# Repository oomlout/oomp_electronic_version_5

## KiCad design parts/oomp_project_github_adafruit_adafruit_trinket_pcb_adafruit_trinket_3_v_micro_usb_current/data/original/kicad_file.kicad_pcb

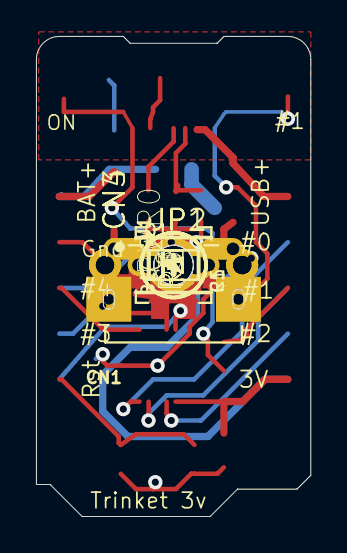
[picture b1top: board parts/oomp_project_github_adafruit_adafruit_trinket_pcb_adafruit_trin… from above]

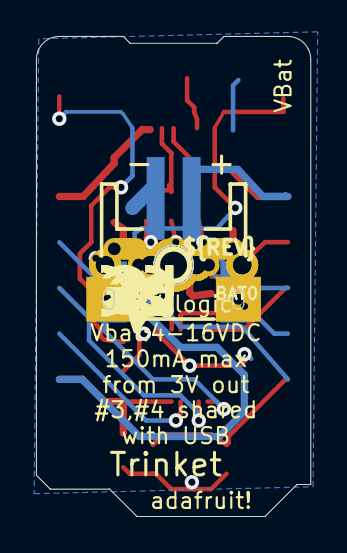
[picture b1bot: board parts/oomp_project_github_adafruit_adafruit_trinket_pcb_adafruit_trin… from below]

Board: 16 copper layers, 15.2 x 26.7 mm, 30 parts (5 on the bottom side), 15 nets.

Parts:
B1: red; CHIPLED_0805_NOOUTLINE
BAT0: JSTPH2
C1, C8: 10uF; 0805-NO
CN1: 4UCONN_20329
CN3, CN4: 1X4-CLEANBIG; 1X04-CLEANBIG
D2, D3: SCHOTTKY; SOD-123FL
IC2: MIC5225-3.3v; SOT23-5L
JP1, JP2: 1X01-CLEANBIG
PWR0: green; CHIPLED_0805_NOOUTLINE
Q1: reset; BTN_KMR2_4.6X2.8
R1, R2: 68 (0603); 0603-NO
R3: 1.5K (0603); 0603-NO
R4, R5: 470 (0603); 0603-NO
U1: MLF20_4X4MM_0.5MM_ATMEL
U$1, U$6: FIDUCIAL""; FIDUCIAL_1MM
U$5: ADAFRUIT_3.5MM
U$8, U$9: MOUNTINGHOLE2.0; MOUNTINGHOLE_2.0_PLATED
U$12: PCBFEAT-REV-040
U$13: SYMBOL_FCC_TINY
U$14: SYMBOL_CE_TINY
UNK_HOLE_0: dummyfp0
UNK_HOLE_1: dummyfp1

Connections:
+3V3: C8.1, CN4.1, IC2.5, R3.2, R4.2, U1.15
B0: CN4.4, U1.11
B1: CN4.3, R5.2, U1.12
B2: CN4.2, U1.14
B3: CN3.2, R1.2, U1.2
B4: CN3.3, R2.2, U1.5
D+: CN1.D+, R2.1
D-: CN1.D-, R1.1, R3.1
GND: B1.C, BAT0.1, C1.2, C8.2, CN1.BASE@1, CN1.BASE@2, CN1.GND, CN1.SPRT@1, CN1.SPRT@2, CN1.SPRT@3, CN1.SPRT@4, CN3.4, IC2.2, PWR0.C, Q1.B, Q1.B', U1.8, U1.THERMAL
unnamed: B1.A, R5.1
unnamed: PWR0.A, R4.1
unnamed: C1.1, D2.C, D3.C, IC2.1, IC2.3
RESET: CN3.1, Q1.A, Q1.A', U1.1
VBAT: BAT0.2, D3.A, JP2.1
VBUS: CN1.VBUS, D2.A, JP1.1

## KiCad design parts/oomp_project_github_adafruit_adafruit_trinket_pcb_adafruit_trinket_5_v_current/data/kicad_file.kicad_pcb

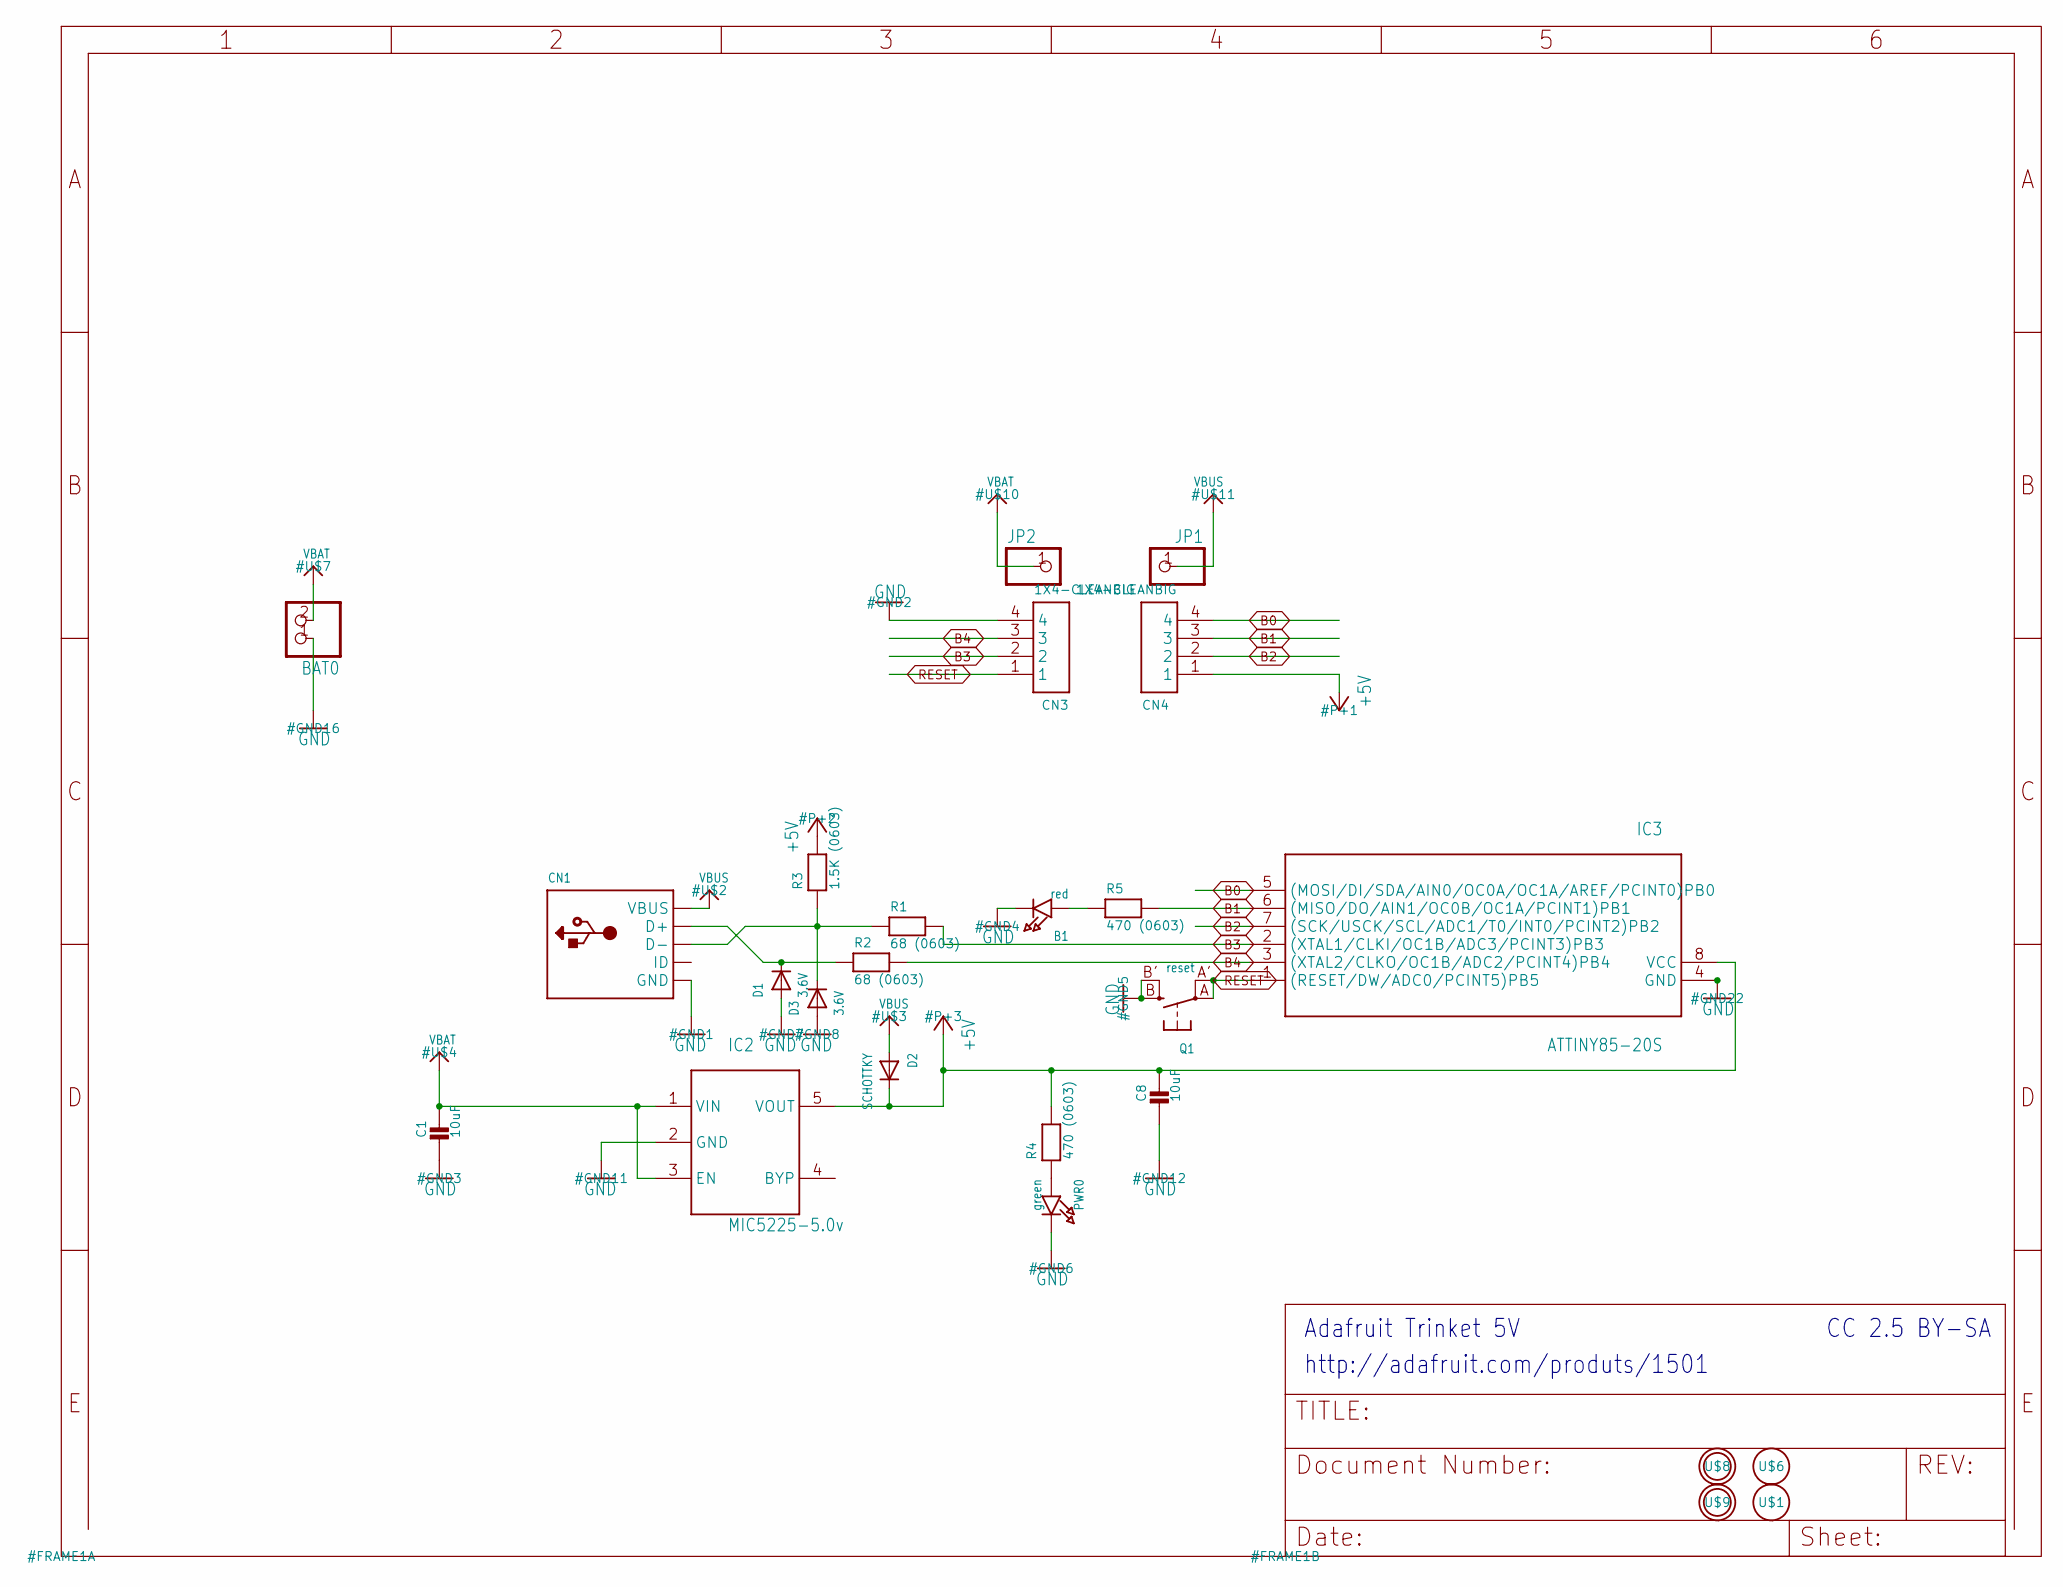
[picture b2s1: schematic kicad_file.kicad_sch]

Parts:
B1: red; CHIPLED_0805_NOOUTLINE
BAT0: CON_JST_PH_2PIN; JSTPH2
C1, C8: 10uF; 0805-NO
CN1: USBMINIB; USB-MINIB
CN3, CN4: 1X4-CLEANBIG; 1X04-CLEANBIG
D1, D3: 3.6V; SOD-323
D2: SCHOTTKY; SOD-123FL
IC2: MIC5225-5.0v; SOT23-5L
IC3: ATTINY85-20S; SOIC8
JP1, JP2: PINHD-1X1CB; 1X01-CLEANBIG
PWR0: green; CHIPLED_0805_NOOUTLINE
Q1: reset; BTN_KMR2_4.6X2.8
R1, R2: 68 (0603); 0603-NO
R3: 1.5K (0603); 0603-NO
R4, R5: 470 (0603); 0603-NO
U$1, U$6: FIDUCIAL; FIDUCIAL_1MM
U$8, U$9: MOUNTINGHOLE2.0; MOUNTINGHOLE_2.0_PLATED

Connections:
+5V: C8.1, CN4.1, D2.C, IC2.5 (VOUT), IC3.8 (VCC), R3.2, R4.2
B0: CN4.4, IC3.5 ((MOSI/DI/SDA/AIN0/OC0A/OC1A/AREF/PCINT0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)
B1: CN4.3, IC3.6 ((MISO/DO/AIN1/OC0B/OC1A/PCINT1)PB1), R5.2
B2: CN4.2, IC3.7 ((SCK/USCK/SCL/ADC1/T0/INT0/PCINT2)PB2)
B3: CN3.2, IC3.2 ((XTAL1/CLKI/OC1B/ADC3/PCINT3)PB3), R1.2
B4: CN3.3, IC3.3 ((XTAL2/CLKO/OC1B/ADC2/PCINT4)PB4), R2.2
GND: B1.C, BAT0.1, C1.2, C8.2, CN1.GND, CN1.GND1 (GND), CN1.GND2 (GND), CN1.GND3 (GND), CN1.GND4 (GND), CN3.4, D1.A, D3.A, IC2.2 (GND), IC3.4 (GND), PWR0.C, Q1.B (S), Q1.B' (S1)
unnamed: B1.A, R5.1
unnamed: CN1.D+, D1.C, R2.1
unnamed: CN1.D-, D3.C, R1.1, R3.1
unnamed: PWR0.A, R4.1
RESET: CN3.1, IC3.1 ((RESET/DW/ADC0/PCINT5)PB5), Q1.A, Q1.A' (P1)
VBAT: BAT0.2, C1.1, IC2.1 (VIN), IC2.3 (EN), JP2.1
VBUS: CN1.VBUS, D2.A, JP1.1

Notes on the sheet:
CC 2.5 BY-SA
Adafruit Trinket 5V
http://adafruit.com/produts/1501

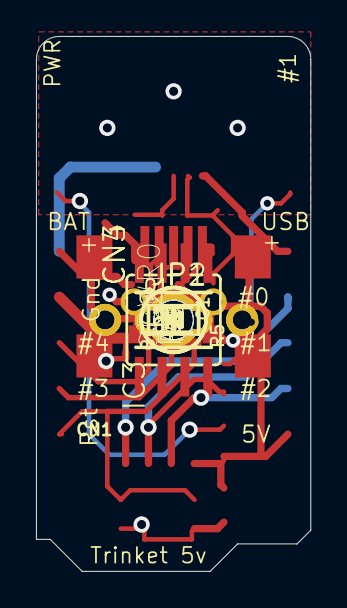
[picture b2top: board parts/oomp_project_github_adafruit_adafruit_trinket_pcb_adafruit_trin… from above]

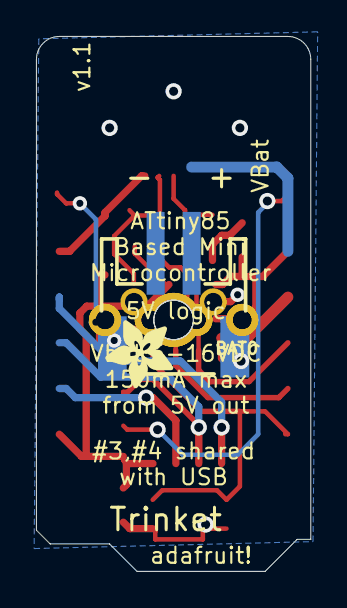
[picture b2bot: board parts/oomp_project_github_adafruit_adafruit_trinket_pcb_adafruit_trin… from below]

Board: 16 copper layers, 15.2 x 29.7 mm, 28 parts (2 on the bottom side), 14 nets.

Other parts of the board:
U$5: ADAFRUIT_3.5MM
UNK_HOLE_0: dummyfp0
UNK_HOLE_1: dummyfp1

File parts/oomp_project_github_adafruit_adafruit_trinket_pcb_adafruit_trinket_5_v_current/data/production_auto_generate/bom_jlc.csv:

Comment,Designator,Footprint,LCSC Part #
,"JP1,JP2",Adafruit Trinket 5V-import-fps:1X01-CLEANBIG,C7501259
,U$5,Adafruit Trinket 5V-import-fps:ADAFRUIT_3.5MM,
,BAT0,Adafruit Trinket 5V-import-fps:JSTPH2,
,CN1,Adafruit Trinket 5V-import-fps:USB-MINIB,
1.5K (0603),R3,Adafruit Trinket 5V-import-fps:0603-NO,C2930050
10uF,"C1,C8",Adafruit Trinket 5V-import-fps:0805-NO,
1X4-CLEANBIG,"CN3,CN4",Adafruit Trinket 5V-import-fps:1X04-CLEANBIG,
3.6V,"D1,D3",Adafruit Trinket 5V-import-fps:SOD-323,
470 (0603),"R4,R5",Adafruit Trinket 5V-import-fps:0603-NO,C23179
68 (0603),"R1,R2",Adafruit Trinket 5V-import-fps:0603-NO,C27592
ATTINY85-20S,IC3,Adafruit Trinket 5V-import-fps:SOIC8,
FIDUCIAL,"U$1,U$6",Adafruit Trinket 5V-import-fps:FIDUCIAL_1MM,
green,PWR0,Adafruit Trinket 5V-import-fps:CHIPLED_0805_NOOUTLINE,
MIC5225-5.0v,IC2,Adafruit Trinket 5V-import-fps:SOT23-5L,
red,B1,Adafruit Trinket 5V-import-fps:CHIPLED_0805_NOOUTLINE,
reset,Q1,Adafruit Trinket 5V-import-fps:BTN_KMR2_4.6X2.8,
SCHOTTKY,D2,Adafruit Trinket 5V-import-fps:SOD-123FL,

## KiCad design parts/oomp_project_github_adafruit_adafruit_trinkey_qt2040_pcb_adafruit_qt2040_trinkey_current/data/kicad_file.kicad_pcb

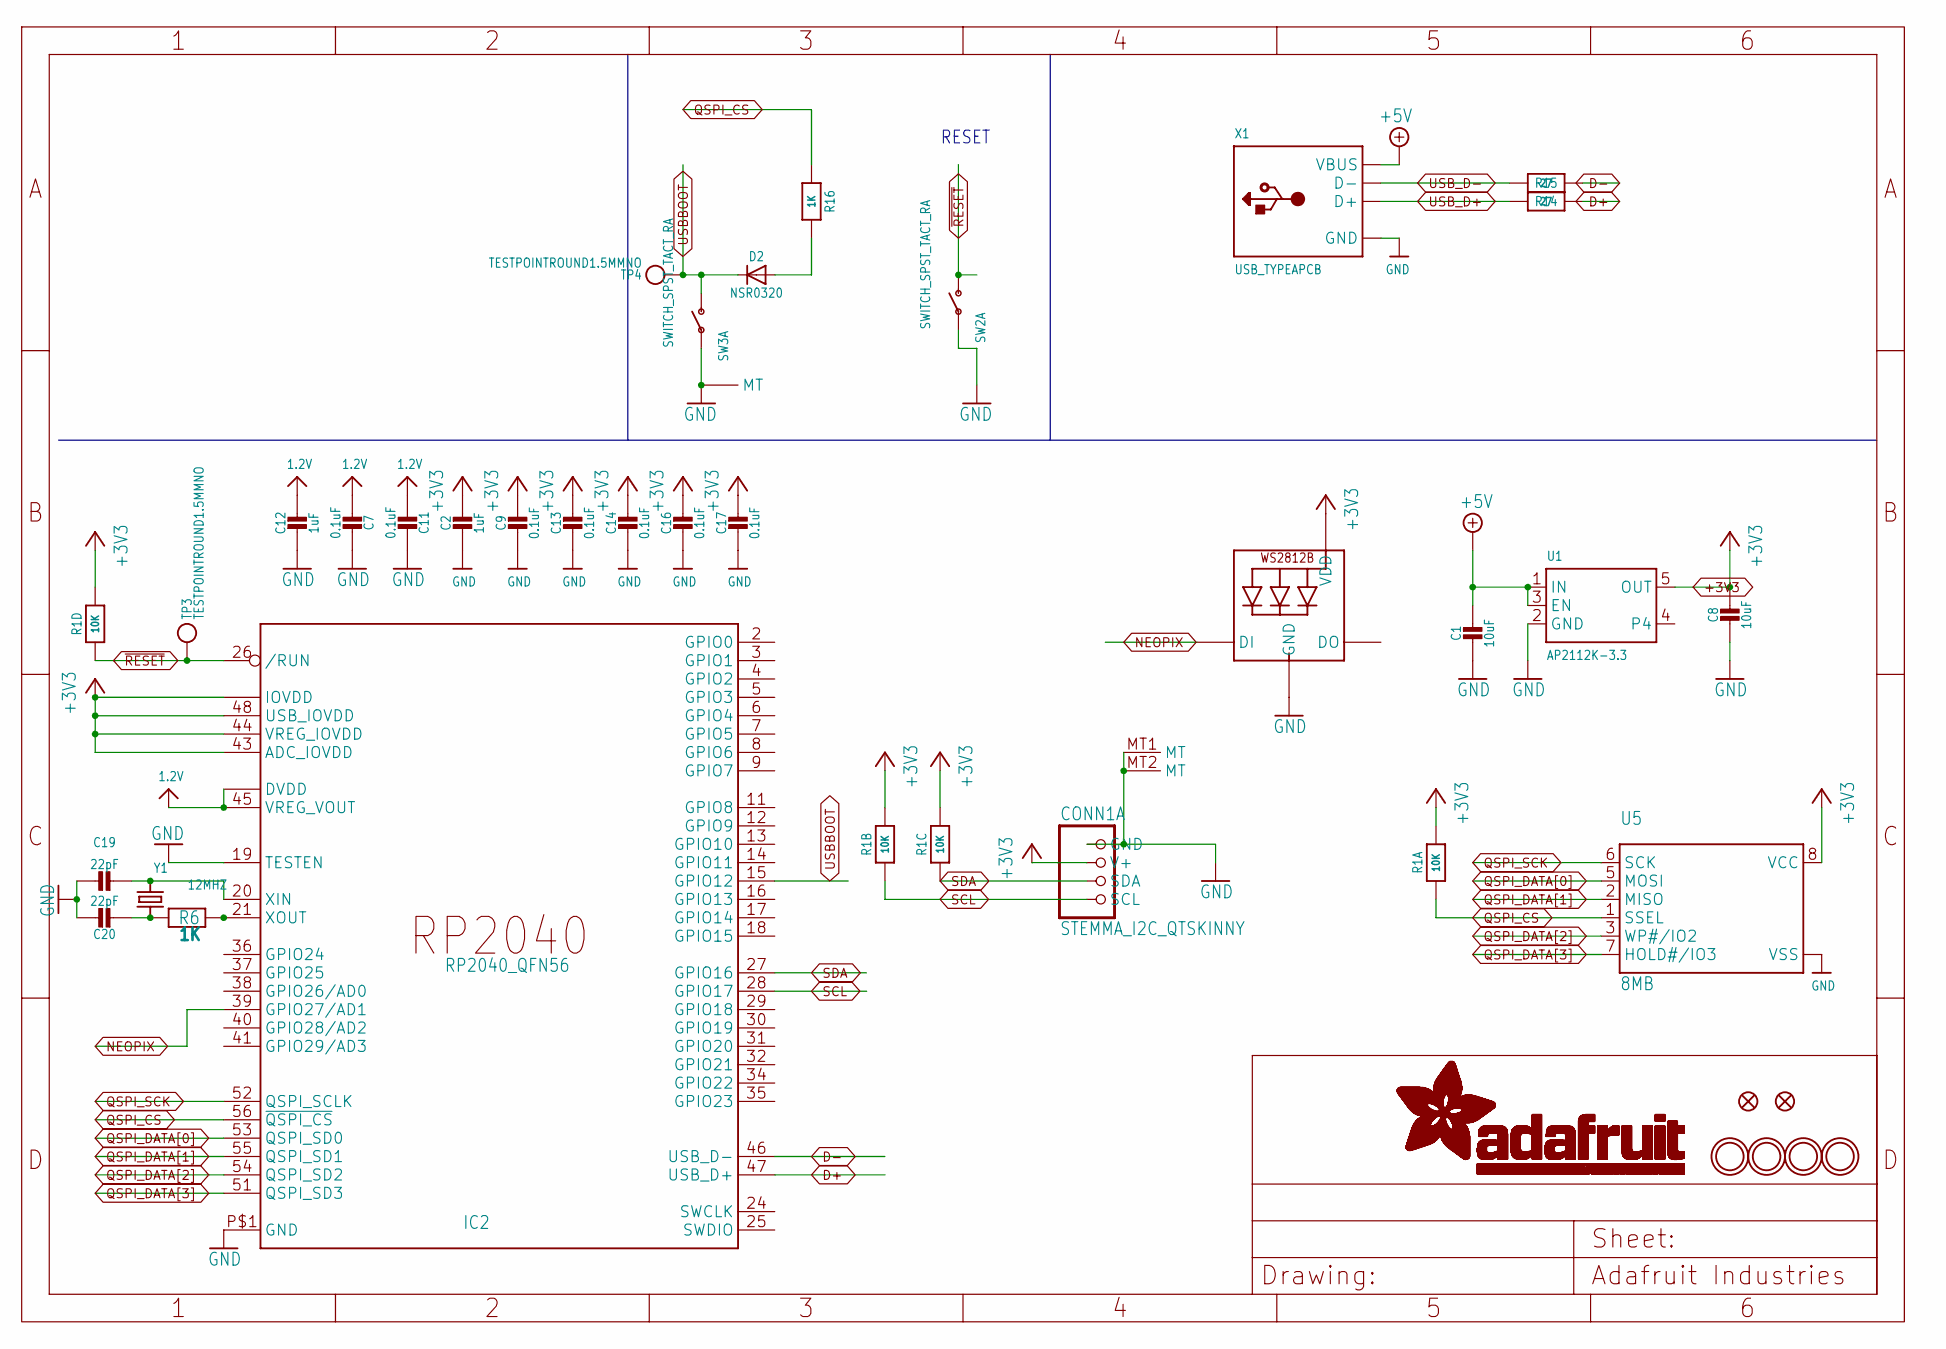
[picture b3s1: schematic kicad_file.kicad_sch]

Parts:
C1, C8: 10uF; 0805-NO
C2, C12: 1uF; 0603-NO
C7: 0.1uF; _0603MP
C9, C11, C13, C14, C16, C17: 0.1uF; 0603-NO
C19, C20: 22pF; 0603-NO
CONN1: STEMMA_I2C_QTSKINNY; JST_SH4_SKINNY
D2: NSR0320; SOD-323_MINI
IC2: RP2040_QFN56; QFN56_7MM_REDUCEDEPAD
LED1: WS2812B_SK6805_1515; SK6805_1515
R1: 10K; RESPACK_4X0603
R6, R16: 1K; 0603-NO
R14, R15: 27; 0603-NO
SW2, SW3: SWITCH_SPST_TACT_RA; SPST_TACTILE_RA
TP3, TP4: TESTPOINTROUND1.5MMNO; TESTPOINT_ROUND_1.5MM_NO
U1: AP2112K-3.3; SOT23-5
U5: 8MB; USON8_4X4
U$1, U$2, U$4, U$5: MOUNTINGHOLE2.5; MOUNTINGHOLE_2.5_PLATED
U$6, U$8: FIDUCIAL_1MM
X1: USB_TYPEAPCB; USBA_PCB
Y1: 12MHZ; CRYSTAL_2.5X2

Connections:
1.2V: C7.2, C11.2, C12.1, IC2.23 (DVDD), IC2.45 (VREG_VOUT), IC2.50 (DVDD)
+3V3: C2.1, C8.1, C9.1, C13.1, C14.1, C16.1, C17.1, CONN1.2 (V+), IC2.1 (IOVDD), IC2.10 (IOVDD), IC2.22 (IOVDD), IC2.33 (IOVDD), IC2.42 (IOVDD), IC2.43 (ADC_IOVDD), IC2.44 (VREG_IOVDD), IC2.48 (USB_IOVDD), IC2.49 (IOVDD), LED1.2 (VDD), R1.5 (2), R1.6 (2), R1.7 (2), R1.8 (2), U1.5 (OUT), U5.8 (VCC)
+5V: C1.1, U1.1 (IN), U1.3 (EN), X1.VCC (VBUS)
D+: IC2.47 (USB_D+), R15.2
D-: IC2.46 (USB_D-), R14.2
GND: C1.2, C2.2, C7.1, C8.2, C9.2, C11.1, C12.2, C13.2, C14.2, C16.2, C17.2, C19.1, C20.1, CONN1.1 (GND), CONN1.MT1 (MT), CONN1.MT2 (MT), IC2.19 (TESTEN), IC2.P$1 (GND), LED1.4 (GND), SW2.1, SW3.1, SW3.MT1 (MT), SW3.MT2 (MT), U1.2 (GND), U5.4 (VSS), U5.PAD (VSS), X1.GND
unnamed: D2.A, R16.2
unnamed: C19.2, IC2.20 (XIN), Y1.3 (2)
unnamed: C20.2, R6.1, Y1.1
unnamed: IC2.21 (XOUT), R6.2
NEOPIX: IC2.39 (GPIO27/AD1), LED1.1 (DI)
QSPI_CS: IC2.56 (~QSPI_CS), R1.1, R16.1, U5.1 (SSEL)
QSPI_DATA[0]: IC2.53 (QSPI_SD0), U5.5 (MOSI)
QSPI_DATA[1]: IC2.55 (QSPI_SD1), U5.2 (MISO)
QSPI_DATA[2]: IC2.54 (QSPI_SD2), U5.3 (WP#/IO2)
QSPI_DATA[3]: IC2.51 (QSPI_SD3), U5.7 (HOLD#/IO3)
QSPI_SCK: IC2.52 (QSPI_SCLK), U5.6 (SCK)
SCL: CONN1.4 (SCL), IC2.28 (GPIO17), R1.2 (1)
SDA: CONN1.3 (SDA), IC2.27 (GPIO16), R1.3 (1)
USBBOOT: D2.C, IC2.15 (GPIO12), SW3.2 (S), TP4.P$1
USB_D+: R15.1, X1.USB_PLUS (D+)
USB_D-: R14.1, X1.USB_NEG (D-)
~RESET: IC2.26 (/RUN), R1.4 (1), SW2.2 (S), TP3.P$1

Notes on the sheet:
RESET

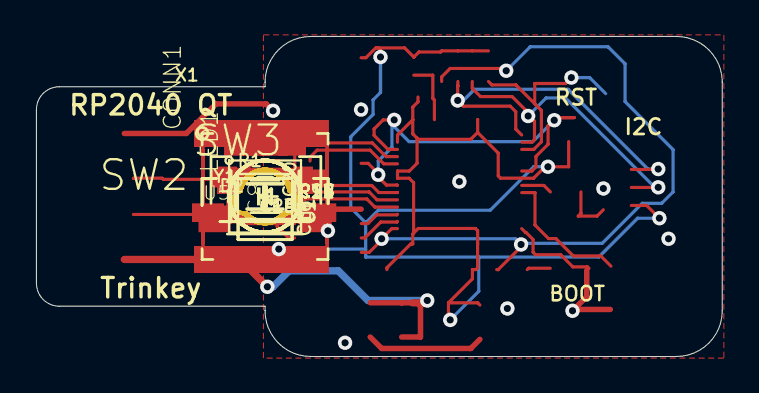
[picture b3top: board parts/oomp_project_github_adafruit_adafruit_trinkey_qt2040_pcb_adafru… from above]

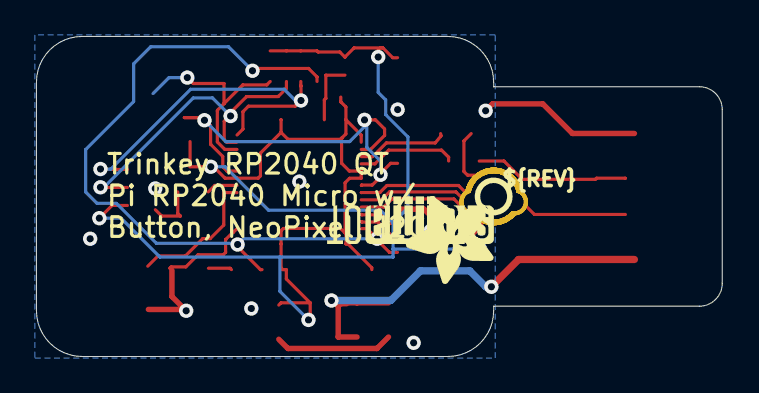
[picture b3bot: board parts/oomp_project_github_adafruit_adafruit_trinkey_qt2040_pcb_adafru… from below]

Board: 16 copper layers, 38.1 x 17.8 mm, 39 parts (5 on the bottom side), 23 nets.

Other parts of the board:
U$7: STEMMAQT
U$9: PCBFEAT-REV-040
U$10: ADAFRUIT_5MM

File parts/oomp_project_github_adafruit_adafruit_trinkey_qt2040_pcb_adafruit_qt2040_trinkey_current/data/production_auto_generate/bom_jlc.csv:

Comment,Designator,Footprint,LCSC Part #
,U$10,Adafruit QT2040 Trinkey-import-fps:ADAFRUIT_5MM,
,U$9,Adafruit QT2040 Trinkey-import-fps:PCBFEAT-REV-040,
,"SW2,SW3",Adafruit QT2040 Trinkey-import-fps:SPST_TACTILE_RA,
,U$7,Adafruit QT2040 Trinkey-import-fps:STEMMAQT,
,"TP3,TP4",Adafruit QT2040 Trinkey-import-fps:TESTPOINT_ROUND_1.5MM_NO,
,X1,Adafruit QT2040 Trinkey-import-fps:USBA_PCB,
  NSR0320,D2,Adafruit QT2040 Trinkey-import-fps:SOD-323_MINI,
0.1uF,"C9,C11,C13,C14,C16,C17",Adafruit QT2040 Trinkey-import-fps:0603-NO,C14663
0.1uF,C7,Adafruit QT2040 Trinkey-import-fps:_0603MP,C14663
10K,R1,Adafruit QT2040 Trinkey-import-fps:RESPACK_4X0603,C98220
10uF,"C1,C8",Adafruit QT2040 Trinkey-import-fps:0805-NO,
12MHZ,Y1,Adafruit QT2040 Trinkey-import-fps:CRYSTAL_2.5X2,
1K,"R6,R16",Adafruit QT2040 Trinkey-import-fps:0603-NO,C2907002
1uF,"C2,C12",Adafruit QT2040 Trinkey-import-fps:0603-NO,C5673
22pF,"C19,C20",Adafruit QT2040 Trinkey-import-fps:0603-NO,C105620
27,"R14,R15",Adafruit QT2040 Trinkey-import-fps:0603-NO,C25190
8MB,U5,Adafruit QT2040 Trinkey-import-fps:USON8_4X4,
AP2112K-3.3,U1,Adafruit QT2040 Trinkey-import-fps:SOT23-5,
FIDUCIAL_1MM,"U$6,U$8",Adafruit QT2040 Trinkey-import-fps:FIDUCIAL_1MM,
RP2040_QFN56,IC2,Adafruit QT2040 Trinkey-import-fps:QFN56_7MM_REDUCEDEPAD,
STEMMA_I2C_QTSKINNY,CONN1,Adafruit QT2040 Trinkey-import-fps:JST_SH4_SKINNY,
WS2812B_SK6805_1515,LED1,Adafruit QT2040 Trinkey-import-fps:SK6805_1515,

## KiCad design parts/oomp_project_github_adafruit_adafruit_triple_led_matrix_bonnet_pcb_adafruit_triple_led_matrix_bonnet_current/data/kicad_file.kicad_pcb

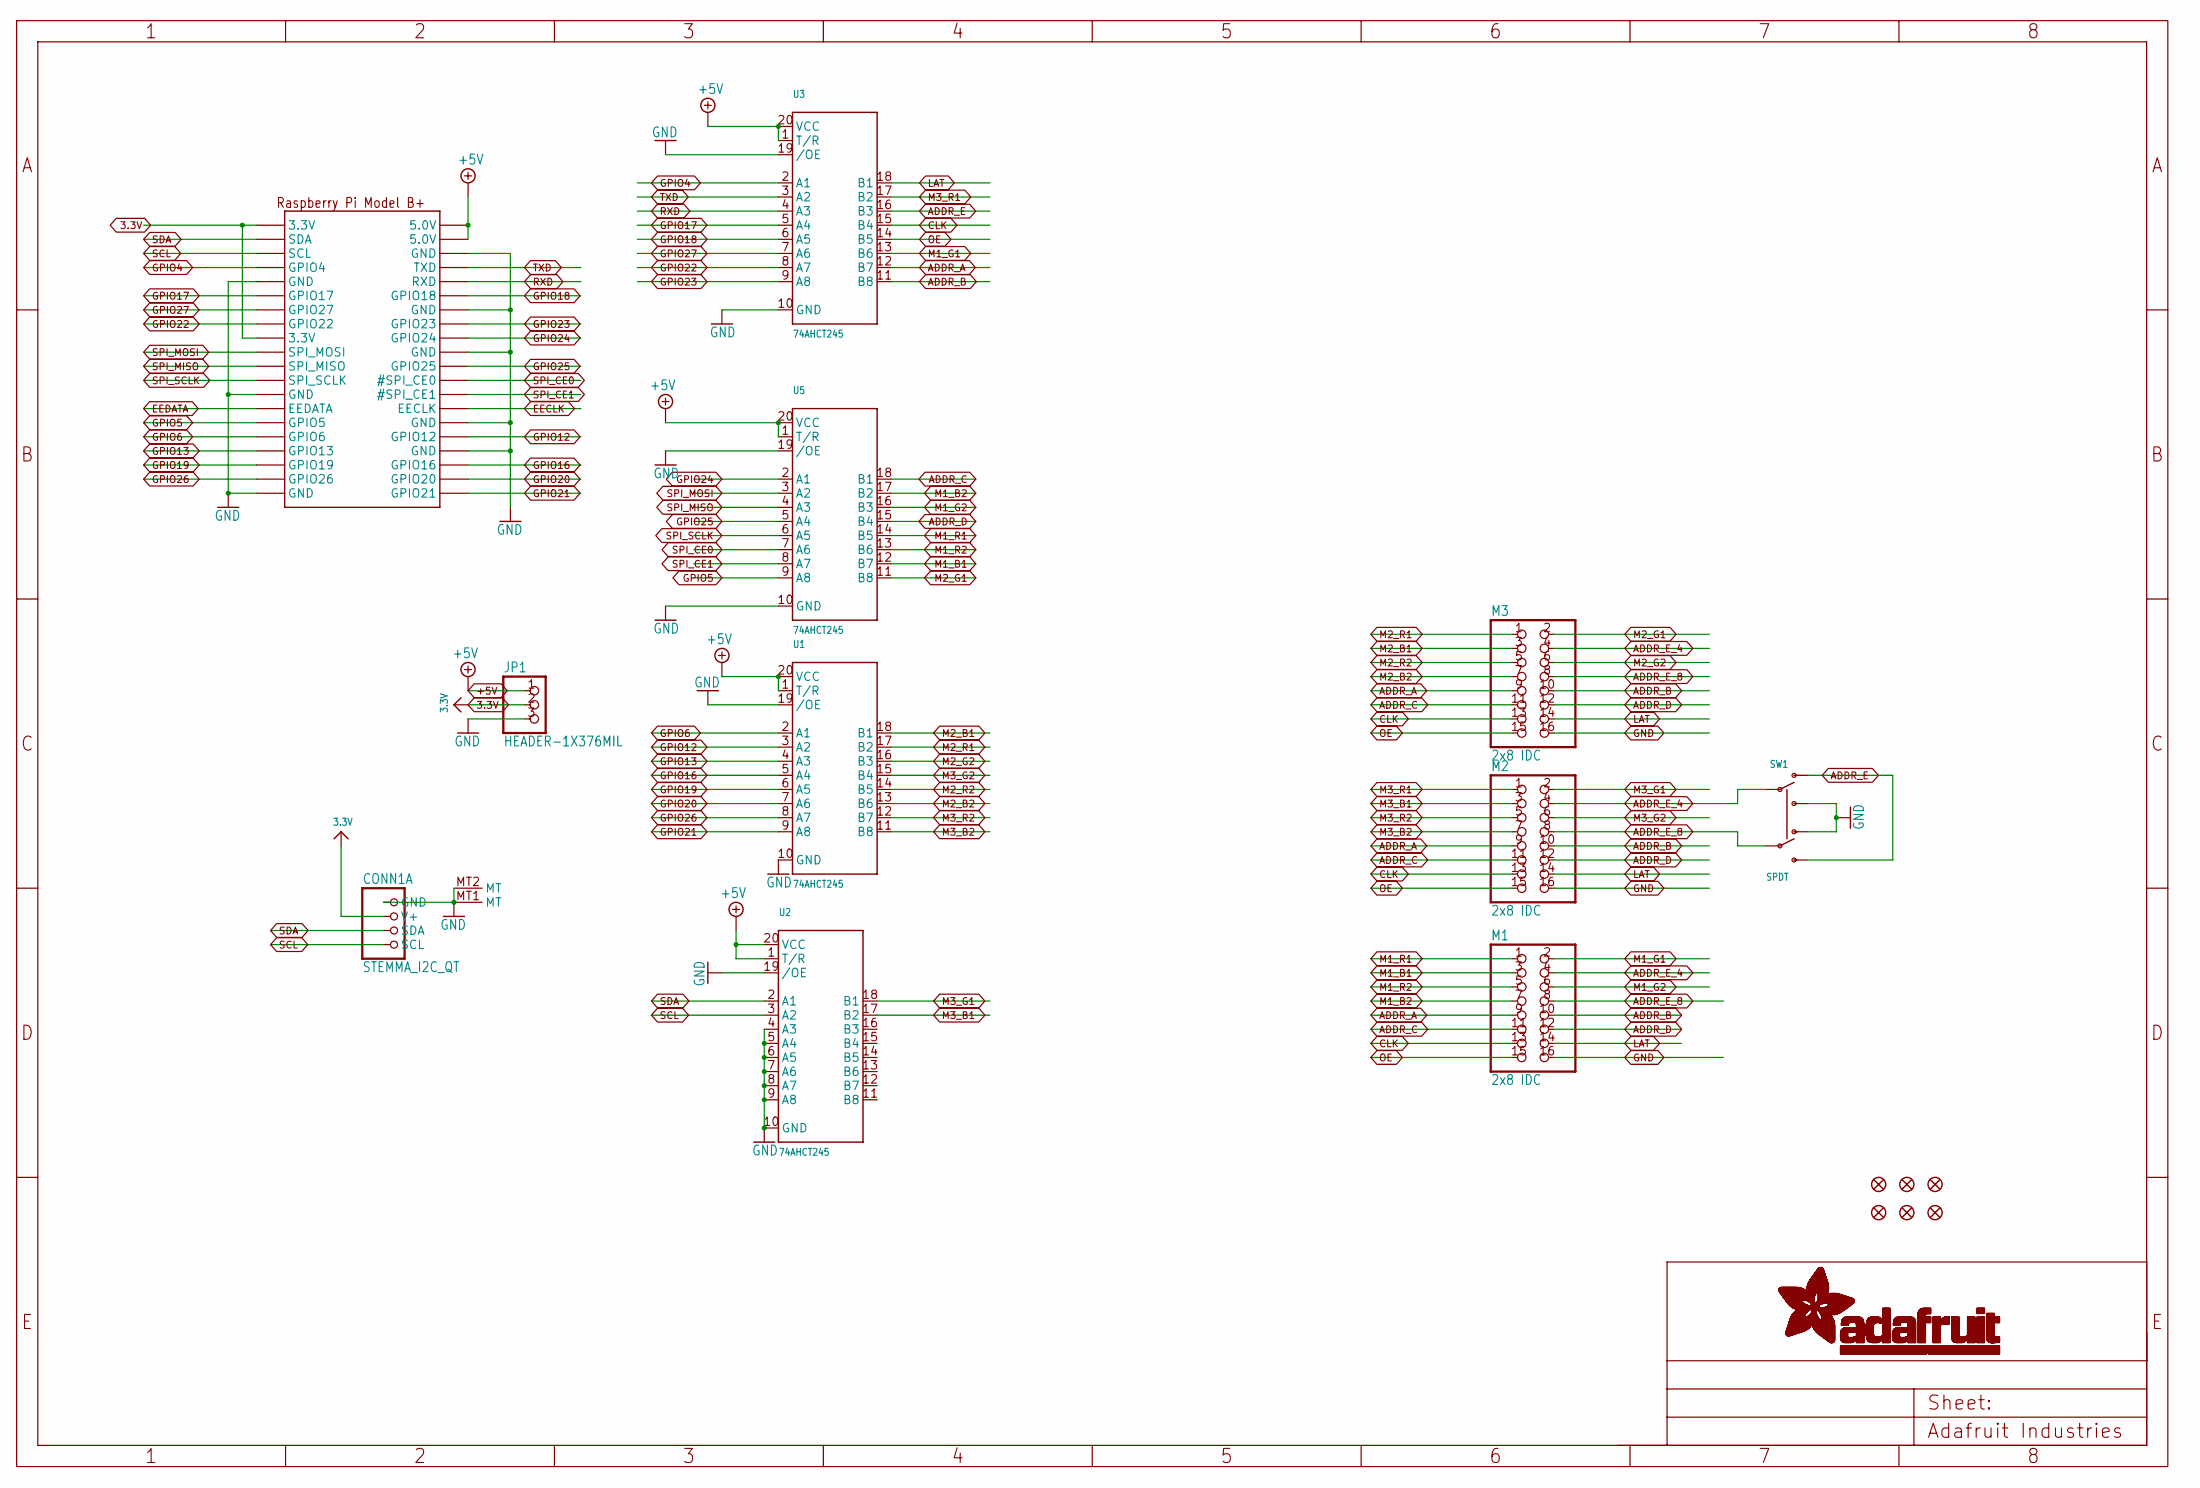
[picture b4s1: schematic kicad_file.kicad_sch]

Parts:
CONN1: STEMMA_I2C_QT; JST_SH4; LCSC C2845363
FID1, FID2, FID3, FID4, FID5, FID6: FIDUCIAL_1MM
JP1: HEADER-1X376MIL; 1X03_ROUND_76
M1, M2, M3: 2x8 IDC; 2X08_SHROUDED
RPI1: RASPBERRYPI_BPLUS_2X20_THMSMT; RASPI_2X20_THMSMT
SW1: SPDT; EG1390; LCSC C2837066
U1, U2, U3, U5: 74AHCT245; TSSOP20

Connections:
3.3V: CONN1.2 (V+), JP1.2, RPI1.1 (3.3V), RPI1.17 (3.3V), RPI1.S1 (3.3V), RPI1.S17 (3.3V)
+5V: JP1.1, RPI1.2 (5.0V), RPI1.4 (5.0V), RPI1.S2 (5.0V), RPI1.S4 (5.0V), U1.1 (T/R), U1.20 (VCC), U2.1 (T/R), U2.20 (VCC), U3.1 (T/R), U3.20 (VCC), U5.1 (T/R), U5.20 (VCC)
ADDR_A: M1.9, M2.9, M3.9, U3.12 (B7)
ADDR_B: M1.10, M2.10, M3.10, U3.11 (B8)
ADDR_C: M1.11, M2.11, M3.11, U5.18 (B1)
ADDR_D: M1.12, M2.12, M3.12, U5.15 (B4)
ADDR_E: SW1.O1, SW1.S2, U3.16 (B3)
ADDR_E_4: M1.4, M2.4, M3.4, SW1.P1
ADDR_E_8: M1.8, M2.8, M3.8, SW1.P2
CLK: M1.13, M2.13, M3.13, U3.15 (B4)
EECLK: RPI1.28 (EECLK), RPI1.S28 (EECLK)
EEDATA: RPI1.27 (EEDATA), RPI1.S27 (EEDATA)
GND: CONN1.1 (GND), CONN1.MT1 (MT), CONN1.MT2 (MT), JP1.3, M1.16, M2.16, M3.16, RPI1.6 (GND), RPI1.9 (GND), RPI1.14 (GND), RPI1.20 (GND), RPI1.25 (GND), RPI1.30 (GND), RPI1.34 (GND), RPI1.39 (GND), RPI1.S6 (GND), RPI1.S9 (GND), RPI1.S14 (GND), RPI1.S20 (GND), RPI1.S25 (GND), RPI1.S30 (GND), RPI1.S34 (GND), RPI1.S39 (GND), SW1.O2, SW1.S1, U1.10 (GND), U1.19 (/OE), U2.4 (A3), U2.5 (A4), U2.6 (A5), U2.7 (A6), U2.8 (A7), U2.9 (A8), U2.10 (GND), U2.19 (/OE), U3.10 (GND), U3.19 (/OE), U5.10 (GND), U5.19 (/OE)
GPIO4: RPI1.7 (GPIO4), RPI1.S7 (GPIO4), U3.2 (A1)
GPIO5: RPI1.29 (GPIO5), RPI1.S29 (GPIO5), U5.9 (A8)
GPIO6: RPI1.31 (GPIO6), RPI1.S31 (GPIO6), U1.2 (A1)
GPIO12: RPI1.32 (GPIO12), RPI1.S32 (GPIO12), U1.3 (A2)
GPIO13: RPI1.33 (GPIO13), RPI1.S33 (GPIO13), U1.4 (A3)
GPIO16: RPI1.36 (GPIO16), RPI1.S36 (GPIO16), U1.5 (A4)
GPIO17: RPI1.11 (GPIO17), RPI1.S11 (GPIO17), U3.5 (A4)
GPIO18: RPI1.12 (GPIO18), RPI1.S12 (GPIO18), U3.6 (A5)
GPIO19: RPI1.35 (GPIO19), RPI1.S35 (GPIO19), U1.6 (A5)
GPIO20: RPI1.38 (GPIO20), RPI1.S38 (GPIO20), U1.7 (A6)
GPIO21: RPI1.40 (GPIO21), RPI1.S40 (GPIO21), U1.9 (A8)
GPIO22: RPI1.15 (GPIO22), RPI1.S15 (GPIO22), U3.8 (A7)
GPIO23: RPI1.16 (GPIO23), RPI1.S16 (GPIO23), U3.9 (A8)
GPIO24: RPI1.18 (GPIO24), RPI1.S18 (GPIO24), U5.2 (A1)
GPIO25: RPI1.22 (GPIO25), RPI1.S22 (GPIO25), U5.5 (A4)
GPIO26: RPI1.37 (GPIO26), RPI1.S37 (GPIO26), U1.8 (A7)
GPIO27: RPI1.13 (GPIO27), RPI1.S13 (GPIO27), U3.7 (A6)
LAT: M1.14, M2.14, M3.14, U3.18 (B1)
M1_B1: M1.3, U5.12 (B7)
M1_B2: M1.7, U5.17 (B2)
M1_G1: M1.2, U3.13 (B6)
M1_G2: M1.6, U5.16 (B3)
M1_R1: M1.1, U5.14 (B5)
M1_R2: M1.5, U5.13 (B6)
M2_B1: M3.3, U1.18 (B1)
M2_B2: M3.7, U1.13 (B6)
M2_G1: M3.2, U5.11 (B8)
M2_G2: M3.6, U1.16 (B3)
M2_R1: M3.1, U1.17 (B2)
M2_R2: M3.5, U1.14 (B5)
M3_B1: M2.3, U2.17 (B2)
M3_B2: M2.7, U1.11 (B8)
M3_G1: M2.2, U2.18 (B1)
M3_G2: M2.6, U1.15 (B4)
M3_R1: M2.1, U3.17 (B2)
M3_R2: M2.5, U1.12 (B7)
OE: M1.15, M2.15, M3.15, U3.14 (B5)
RXD: RPI1.10 (RXD), RPI1.S10 (RXD), U3.4 (A3)
SCL: CONN1.4 (SCL), RPI1.5 (SCL), RPI1.S5 (SCL), U2.3 (A2)
SDA: CONN1.3 (SDA), RPI1.3 (SDA), RPI1.S3 (SDA), U2.2 (A1)
SPI_CE0: RPI1.24 (#SPI_CE0), RPI1.S24 (#SPI_CE0), U5.7 (A6)
SPI_CE1: RPI1.26 (#SPI_CE1), RPI1.S26 (#SPI_CE1), U5.8 (A7)
SPI_MISO: RPI1.21 (SPI_MISO), RPI1.S21 (SPI_MISO), U5.4 (A3)
SPI_MOSI: RPI1.19 (SPI_MOSI), RPI1.S19 (SPI_MOSI), U5.3 (A2)
SPI_SCLK: RPI1.23 (SPI_SCLK), RPI1.S23 (SPI_SCLK), U5.6 (A5)
TXD: RPI1.8 (TXD), RPI1.S8 (TXD), U3.3 (A2)

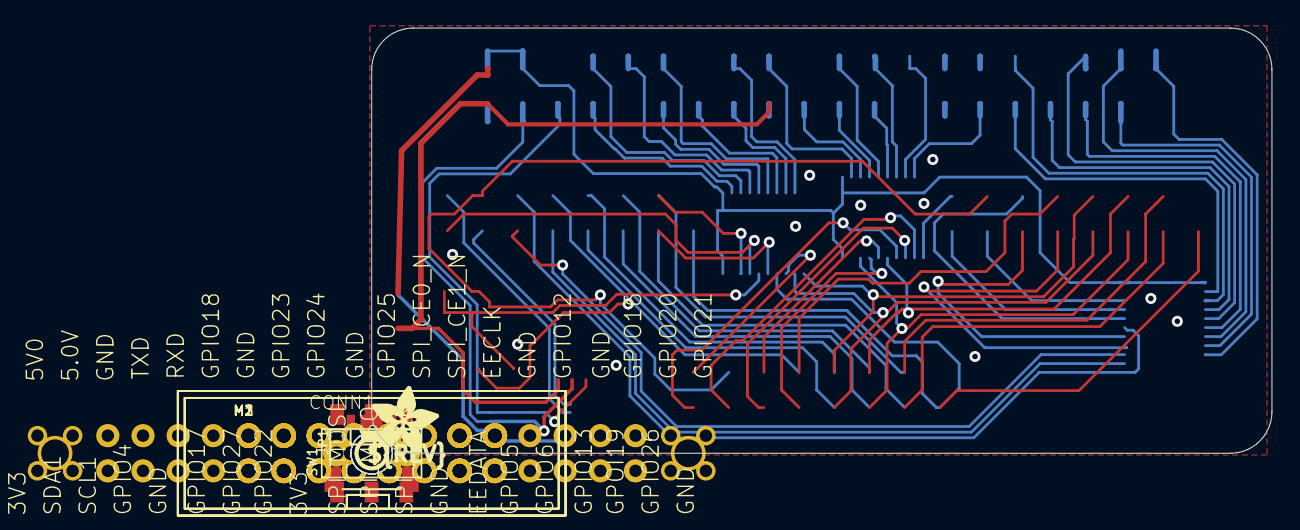
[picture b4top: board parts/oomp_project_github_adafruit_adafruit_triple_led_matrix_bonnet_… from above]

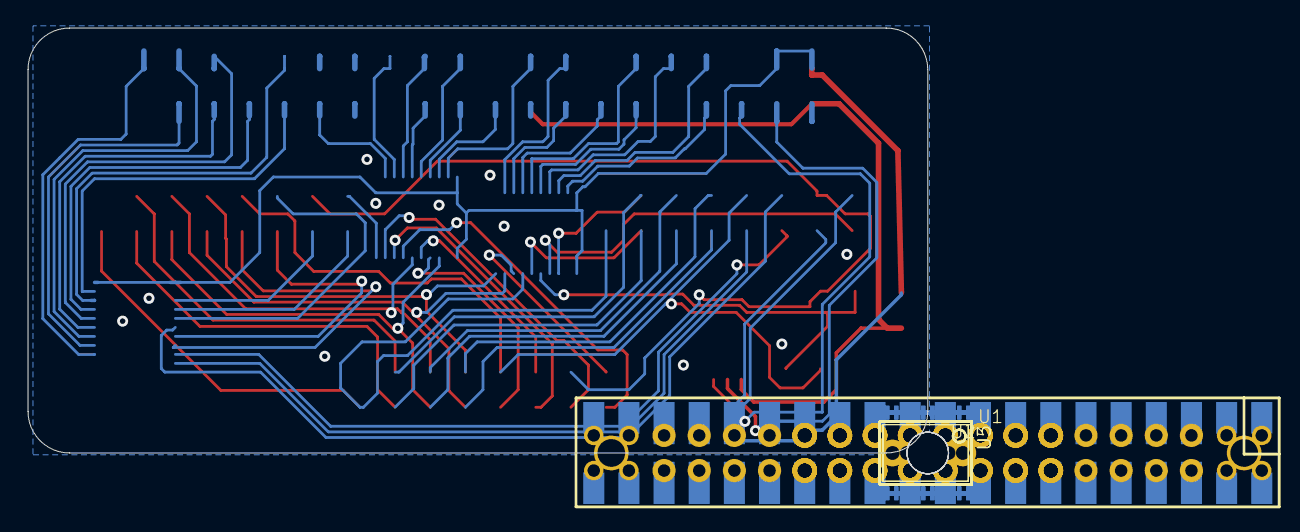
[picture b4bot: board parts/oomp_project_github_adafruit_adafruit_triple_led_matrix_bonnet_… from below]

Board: 2 copper layers, 65.0 x 30.7 mm, 88 parts (61 on the bottom side), 59 nets.

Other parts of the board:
PLABEL0: PLABEL0
PLABEL1: PLABEL1
PLABEL2: PLABEL2
PLABEL3: PLABEL3
PLABEL4: PLABEL4
PLABEL5: PLABEL5
PLABEL6: PLABEL6
PLABEL7: PLABEL7
PLABEL8: PLABEL8
PLABEL9: PLABEL9
PLABEL10: PLABEL10
PLABEL11: PLABEL11
PLABEL12: PLABEL12
PLABEL13: PLABEL13
PLABEL14: PLABEL14
PLABEL15: PLABEL15
PLABEL16: PLABEL16
PLABEL17: PLABEL17
PLABEL18: PLABEL18
PLABEL19: PLABEL19
PLABEL20: PLABEL20
PLABEL21: PLABEL21
PLABEL22: PLABEL22
PLABEL23: PLABEL23
PLABEL24: PLABEL24
PLABEL25: PLABEL25
PLABEL26: PLABEL26
PLABEL27: PLABEL27
PLABEL28: PLABEL28
PLABEL29: PLABEL29
PLABEL30: PLABEL30
PLABEL31: PLABEL31
PLABEL32: PLABEL32
PLABEL33: PLABEL33
PLABEL34: PLABEL34
PLABEL35: PLABEL35
PLABEL36: PLABEL36
PLABEL37: PLABEL37
PLABEL38: PLABEL38
PLABEL39: PLABEL39
PLABEL40: PLABEL40
PLABEL41: PLABEL41
PLABEL42: PLABEL42
PLABEL43: PLABEL43
PLABEL44: PLABEL44
PLABEL45: PLABEL45
PLABEL46: PLABEL46
PLABEL47: PLABEL47
PLABEL48: PLABEL48
PLABEL49: PLABEL49
PLABEL50: PLABEL50
PLABEL51: PLABEL51
PLABEL52: PLABEL52
PLABEL53: PLABEL53
PLABEL54: PLABEL54
PLABEL55: PLABEL55
PLABEL56: PLABEL56
PLABEL57: PLABEL57
PLABEL58: PLABEL58
PLABEL59: PLABEL59
PLABEL60: PLABEL60
PLABEL61: PLABEL61
PLABEL62: PLABEL62
PLABEL63: PLABEL63
PLABEL64: PLABEL64
U$2: ADAFRUIT_5MM
U$3: PCBFEAT-REV-056
UNK_HOLE_0: dummyfp0
UNK_HOLE_1: dummyfp1
UNK_HOLE_2: dummyfp2
UNK_HOLE_3: dummyfp3

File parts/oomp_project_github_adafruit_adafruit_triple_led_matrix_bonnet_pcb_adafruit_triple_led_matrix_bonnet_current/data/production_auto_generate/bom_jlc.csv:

Comment,Designator,Footprint,LCSC Part #
,JP1,Adafruit Triple LED Matrix Bonnet-import-fps:1X03_ROUND_76,C49257
,U$2,Adafruit Triple LED Matrix Bonnet-import-fps:ADAFRUIT_5MM,
,U$3,Adafruit Triple LED Matrix Bonnet-import-fps:PCBFEAT-REV-056,
,PLABEL0,Adafruit Triple LED Matrix Bonnet-import-fps:PLABEL0,
,PLABEL1,Adafruit Triple LED Matrix Bonnet-import-fps:PLABEL1,
,PLABEL10,Adafruit Triple LED Matrix Bonnet-import-fps:PLABEL10,
,PLABEL11,Adafruit Triple LED Matrix Bonnet-import-fps:PLABEL11,
,PLABEL12,Adafruit Triple LED Matrix Bonnet-import-fps:PLABEL12,
,PLABEL13,Adafruit Triple LED Matrix Bonnet-import-fps:PLABEL13,
,PLABEL14,Adafruit Triple LED Matrix Bonnet-import-fps:PLABEL14,
,PLABEL15,Adafruit Triple LED Matrix Bonnet-import-fps:PLABEL15,
,PLABEL16,Adafruit Triple LED Matrix Bonnet-import-fps:PLABEL16,
,PLABEL17,Adafruit Triple LED Matrix Bonnet-import-fps:PLABEL17,
,PLABEL18,Adafruit Triple LED Matrix Bonnet-import-fps:PLABEL18,
,PLABEL19,Adafruit Triple LED Matrix Bonnet-import-fps:PLABEL19,
,PLABEL2,Adafruit Triple LED Matrix Bonnet-import-fps:PLABEL2,
,PLABEL20,Adafruit Triple LED Matrix Bonnet-import-fps:PLABEL20,
,PLABEL21,Adafruit Triple LED Matrix Bonnet-import-fps:PLABEL21,
,PLABEL22,Adafruit Triple LED Matrix Bonnet-import-fps:PLABEL22,
,PLABEL23,Adafruit Triple LED Matrix Bonnet-import-fps:PLABEL23,
,PLABEL24,Adafruit Triple LED Matrix Bonnet-import-fps:PLABEL24,
,PLABEL25,Adafruit Triple LED Matrix Bonnet-import-fps:PLABEL25,
,PLABEL26,Adafruit Triple LED Matrix Bonnet-import-fps:PLABEL26,
,PLABEL27,Adafruit Triple LED Matrix Bonnet-import-fps:PLABEL27,
,PLABEL28,Adafruit Triple LED Matrix Bonnet-import-fps:PLABEL28,
,PLABEL29,Adafruit Triple LED Matrix Bonnet-import-fps:PLABEL29,
,PLABEL3,Adafruit Triple LED Matrix Bonnet-import-fps:PLABEL3,
,PLABEL30,Adafruit Triple LED Matrix Bonnet-import-fps:PLABEL30,
,PLABEL31,Adafruit Triple LED Matrix Bonnet-import-fps:PLABEL31,
,PLABEL32,Adafruit Triple LED Matrix Bonnet-import-fps:PLABEL32,
,PLABEL33,Adafruit Triple LED Matrix Bonnet-import-fps:PLABEL33,
,PLABEL34,Adafruit Triple LED Matrix Bonnet-import-fps:PLABEL34,
,PLABEL35,Adafruit Triple LED Matrix Bonnet-import-fps:PLABEL35,
,PLABEL36,Adafruit Triple LED Matrix Bonnet-import-fps:PLABEL36,
,PLABEL37,Adafruit Triple LED Matrix Bonnet-import-fps:PLABEL37,
,PLABEL38,Adafruit Triple LED Matrix Bonnet-import-fps:PLABEL38,
,PLABEL39,Adafruit Triple LED Matrix Bonnet-import-fps:PLABEL39,
,PLABEL4,Adafruit Triple LED Matrix Bonnet-import-fps:PLABEL4,
,PLABEL40,Adafruit Triple LED Matrix Bonnet-import-fps:PLABEL40,
,PLABEL41,Adafruit Triple LED Matrix Bonnet-import-fps:PLABEL41,
,PLABEL42,Adafruit Triple LED Matrix Bonnet-import-fps:PLABEL42,
,PLABEL43,Adafruit Triple LED Matrix Bonnet-import-fps:PLABEL43,
,PLABEL44,Adafruit Triple LED Matrix Bonnet-import-fps:PLABEL44,
,PLABEL45,Adafruit Triple LED Matrix Bonnet-import-fps:PLABEL45,
,PLABEL46,Adafruit Triple LED Matrix Bonnet-import-fps:PLABEL46,
,PLABEL47,Adafruit Triple LED Matrix Bonnet-import-fps:PLABEL47,
,PLABEL48,Adafruit Triple LED Matrix Bonnet-import-fps:PLABEL48,
,PLABEL49,Adafruit Triple LED Matrix Bonnet-import-fps:PLABEL49,
,PLABEL5,Adafruit Triple LED Matrix Bonnet-import-fps:PLABEL5,
,PLABEL50,Adafruit Triple LED Matrix Bonnet-import-fps:PLABEL50,
,PLABEL51,Adafruit Triple LED Matrix Bonnet-import-fps:PLABEL51,
,PLABEL52,Adafruit Triple LED Matrix Bonnet-import-fps:PLABEL52,
,PLABEL53,Adafruit Triple LED Matrix Bonnet-import-fps:PLABEL53,
,PLABEL54,Adafruit Triple LED Matrix Bonnet-import-fps:PLABEL54,
,PLABEL55,Adafruit Triple LED Matrix Bonnet-import-fps:PLABEL55,
,PLABEL56,Adafruit Triple LED Matrix Bonnet-import-fps:PLABEL56,
,PLABEL57,Adafruit Triple LED Matrix Bonnet-import-fps:PLABEL57,
,PLABEL58,Adafruit Triple LED Matrix Bonnet-import-fps:PLABEL58,
,PLABEL59,Adafruit Triple LED Matrix Bonnet-import-fps:PLABEL59,
,PLABEL6,Adafruit Triple LED Matrix Bonnet-import-fps:PLABEL6,
,PLABEL60,Adafruit Triple LED Matrix Bonnet-import-fps:PLABEL60,
,PLABEL61,Adafruit Triple LED Matrix Bonnet-import-fps:PLABEL61,
,PLABEL62,Adafruit Triple LED Matrix Bonnet-import-fps:PLABEL62,
,PLABEL63,Adafruit Triple LED Matrix Bonnet-import-fps:PLABEL63,
,PLABEL64,Adafruit Triple LED Matrix Bonnet-import-fps:PLABEL64,
,PLABEL7,Adafruit Triple LED Matrix Bonnet-import-fps:PLABEL7,
,PLABEL8,Adafruit Triple LED Matrix Bonnet-import-fps:PLABEL8,
,PLABEL9,Adafruit Triple LED Matrix Bonnet-import-fps:PLABEL9,
2x8 IDC,"M1,M2,M3",Adafruit Triple LED Matrix Bonnet-import-fps:2X08_SHROUDED,
74AHCT245,"U1,U2,U3,U5",Adafruit Triple LED Matrix Bonnet-import-fps:TSSOP20,
RASPBERRYPI_BPLUS_2X20_THMSMT,RPI1,Adafruit Triple LED Matrix Bonnet-import-fps:RASPI_2X20_THMSMT,
SPDT,SW1,Adafruit Triple LED Matrix Bonnet-import-fps:EG1390,
STEMMA_I2C_QT,CONN1,Adafruit Triple LED Matrix Bonnet-import-fps:JST_SH4,C160404
